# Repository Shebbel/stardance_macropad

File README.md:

# stardance_macropad
A 6 key macropad with a rotary encoder and oled display
I started with this macropad guide, because it tought it was a good start regarding future projects. 
It includes a six key macropad with a key matrix, a oled and a rotary encoder 
You can edit the function of the macropad using the VIA website.
I used AI to explain the error codes from the drc and the compiling errors.

| Component | Amount |
|-----:|-----------|
|Seeed XIAO RP2040	| 1x|
|MX-Style switches	  |6x    |
|1N4148 Diodes  |6x       |
|EC11 rotary encoder  |1x       |
|0.91 inch OLED display	  |1x       |
|keycaps  |6x       |
|SK6812 MINI-E LED  |14x       |
|M3x16mm screw	  |4x       |
|M3x5mx4mm heatset insert|4x       |
|case ( 2parts)  |1x       |
|PCB  |1x       |

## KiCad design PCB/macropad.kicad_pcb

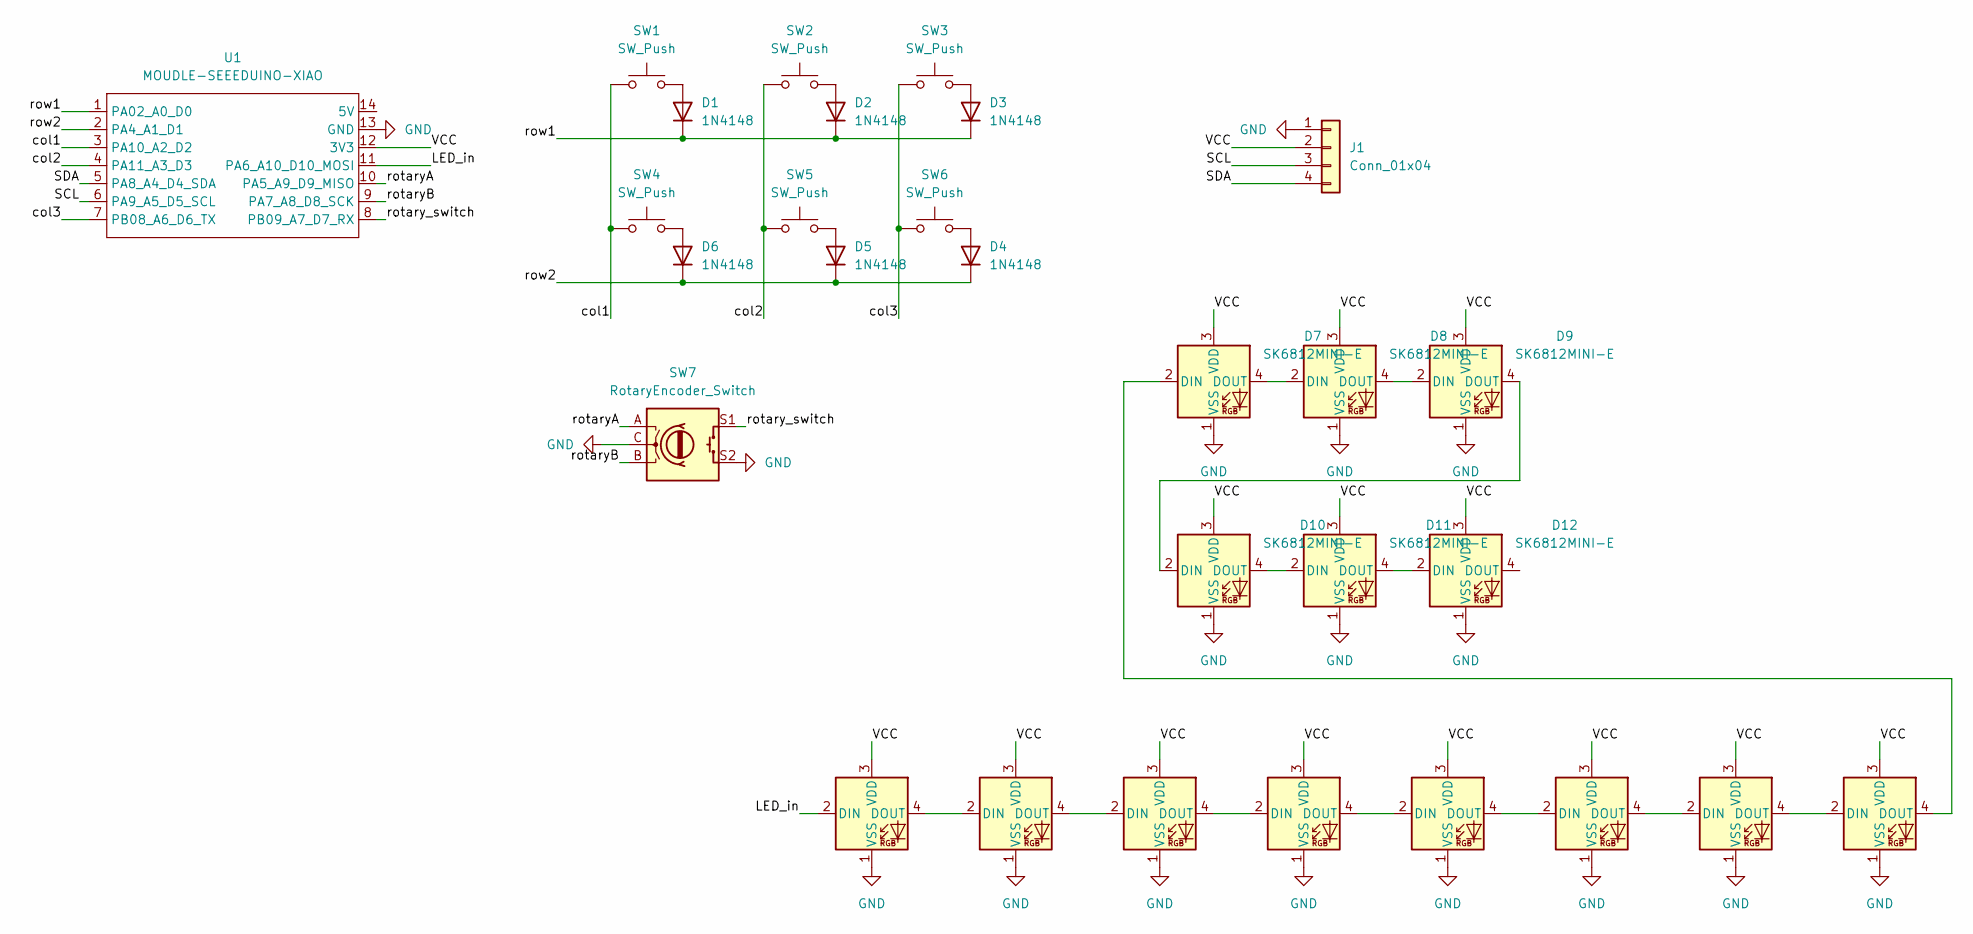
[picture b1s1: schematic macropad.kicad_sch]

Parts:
D1, D2, D3, D4, D5, D6: 1N4148; D_DO-35_SOD27_P7.62mm_Horizontal
D7, D8, D9, D10, D11, D12, D13, D14, D15, D16, D17, D18, D19, D20: SK6812MINI-E; LED_SK6812MINI-E_3.2x2.8mm_P1.5mm_ReverseMount
J1: Conn_01x04; ER_OLEDM0.91_1x-I2C
SW1, SW2, SW3, SW4, SW5, SW6: SW_Push; SW_Cherry_MX_1.00u_PCB
SW7: RotaryEncoder_Switch; RotaryEncoder_Alps_EC11E-Switch_Vertical_H20mm
U1: MOUDLE-SEEEDUINO-XIAO; XIAO-Generic-Hybrid-14P-2.54-21X17.8MM

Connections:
/LED_in: D13.2 (DIN), U1.11 (PA6_A10_D10_MOSI)
/SCL: J1.3, U1.6 (PA9_A5_D5_SCL)
/SDA: J1.4, U1.5 (PA8_A4_D4_SDA)
/VCC: D7.3 (VDD), D8.3 (VDD), D9.3 (VDD), D10.3 (VDD), D11.3 (VDD), D12.3 (VDD), D13.3 (VDD), D14.3 (VDD), D15.3 (VDD), D16.3 (VDD), D17.3 (VDD), D18.3 (VDD), D19.3 (VDD), D20.3 (VDD), J1.2, U1.12 (3V3)
/col1: SW1.1, SW4.1, U1.3 (PA10_A2_D2)
/col2: SW2.1, SW5.1, U1.4 (PA11_A3_D3)
/col3: SW3.1, SW6.1, U1.7 (PB08_A6_D6_TX)
/rotaryA: SW7.A, U1.10 (PA5_A9_D9_MISO)
/rotaryB: SW7.B, U1.9 (PA7_A8_D8_SCK)
/rotary_switch: SW7.S1, U1.8 (PB09_A7_D7_RX)
/row1: D1.1 (K), D2.1 (K), D3.1 (K), U1.1 (PA02_A0_D0)
/row2: D4.1 (K), D5.1 (K), D6.1 (K), U1.2 (PA4_A1_D1)
GND: D7.1 (VSS), D8.1 (VSS), D9.1 (VSS), D10.1 (VSS), D11.1 (VSS), D12.1 (VSS), D13.1 (VSS), D14.1 (VSS), D15.1 (VSS), D16.1 (VSS), D17.1 (VSS), D18.1 (VSS), D19.1 (VSS), D20.1 (VSS), J1.1, SW7.C, SW7.S2, U1.13 (GND)
unnamed: D1.2 (A), SW1.2
unnamed: D2.2 (A), SW2.2
unnamed: D3.2 (A), SW3.2
unnamed: D4.2 (A), SW6.2
unnamed: D5.2 (A), SW5.2
unnamed: D6.2 (A), SW4.2
unnamed: D7.4 (DOUT), D8.2 (DIN)
unnamed: D8.4 (DOUT), D9.2 (DIN)
unnamed: D9.4 (DOUT), D10.2 (DIN)
unnamed: D10.4 (DOUT), D11.2 (DIN)
unnamed: D11.4 (DOUT), D12.2 (DIN)
unnamed: D13.4 (DOUT), D14.2 (DIN)
unnamed: D14.4 (DOUT), D15.2 (DIN)
unnamed: D15.4 (DOUT), D16.2 (DIN)
unnamed: D16.4 (DOUT), D17.2 (DIN)
unnamed: D17.4 (DOUT), D18.2 (DIN)
unnamed: D18.4 (DOUT), D19.2 (DIN)
unnamed: D19.4 (DOUT), D20.2 (DIN)
unnamed: D7.2 (DIN), D20.4 (DOUT)

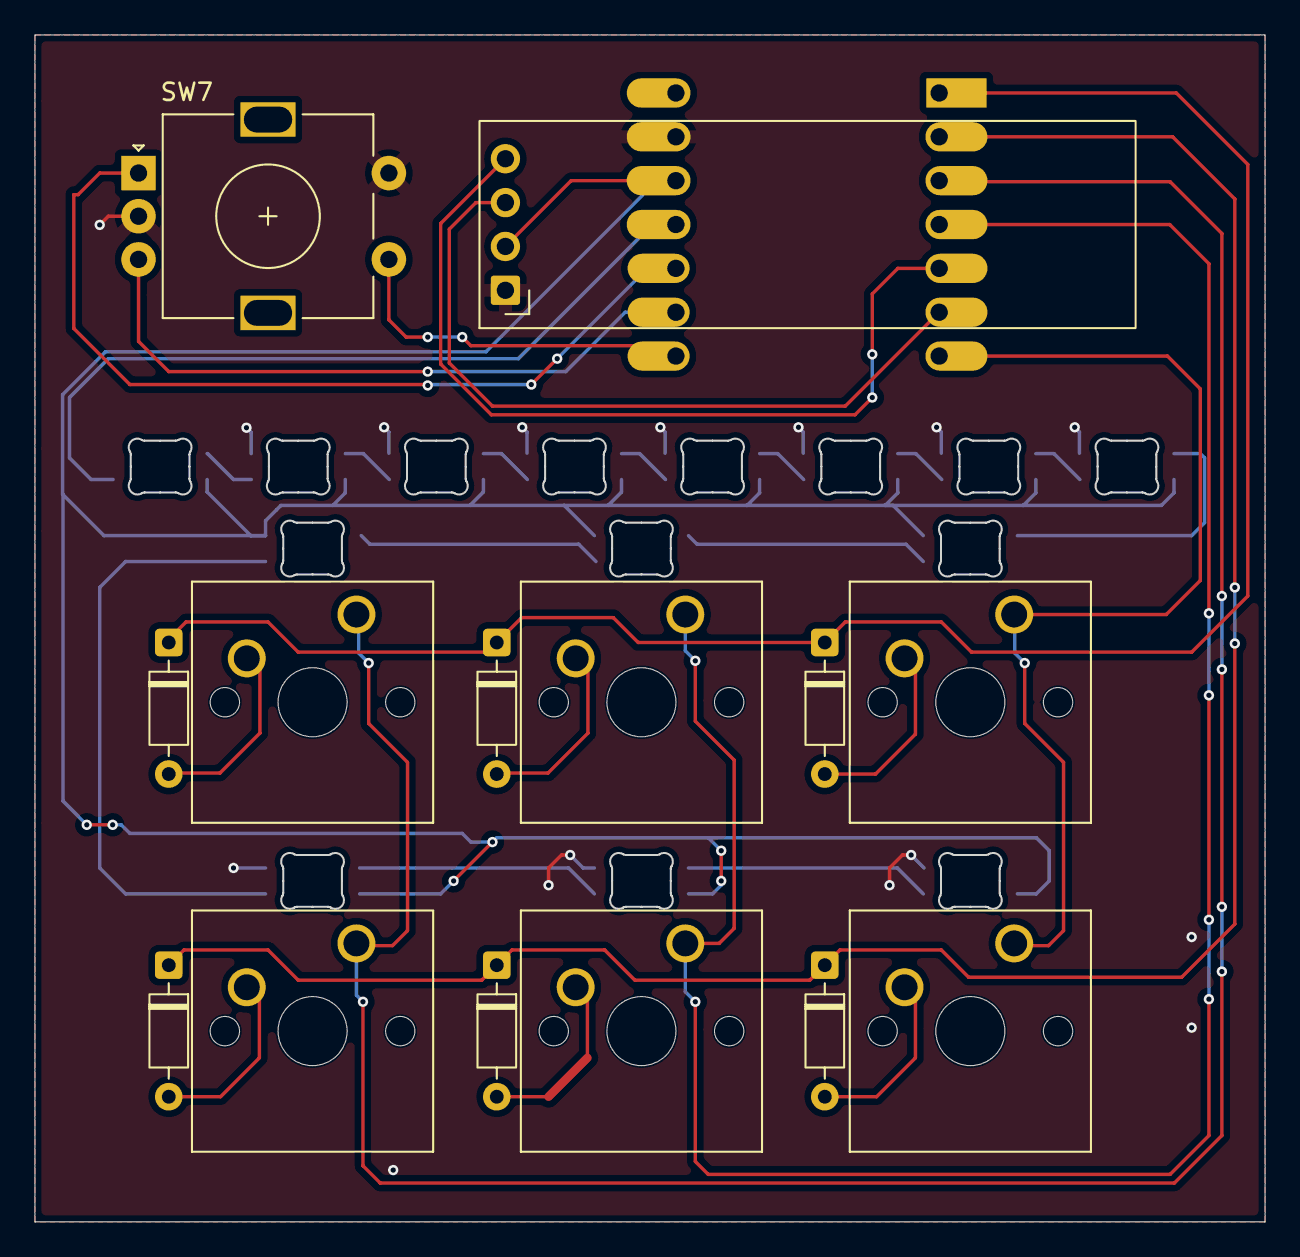
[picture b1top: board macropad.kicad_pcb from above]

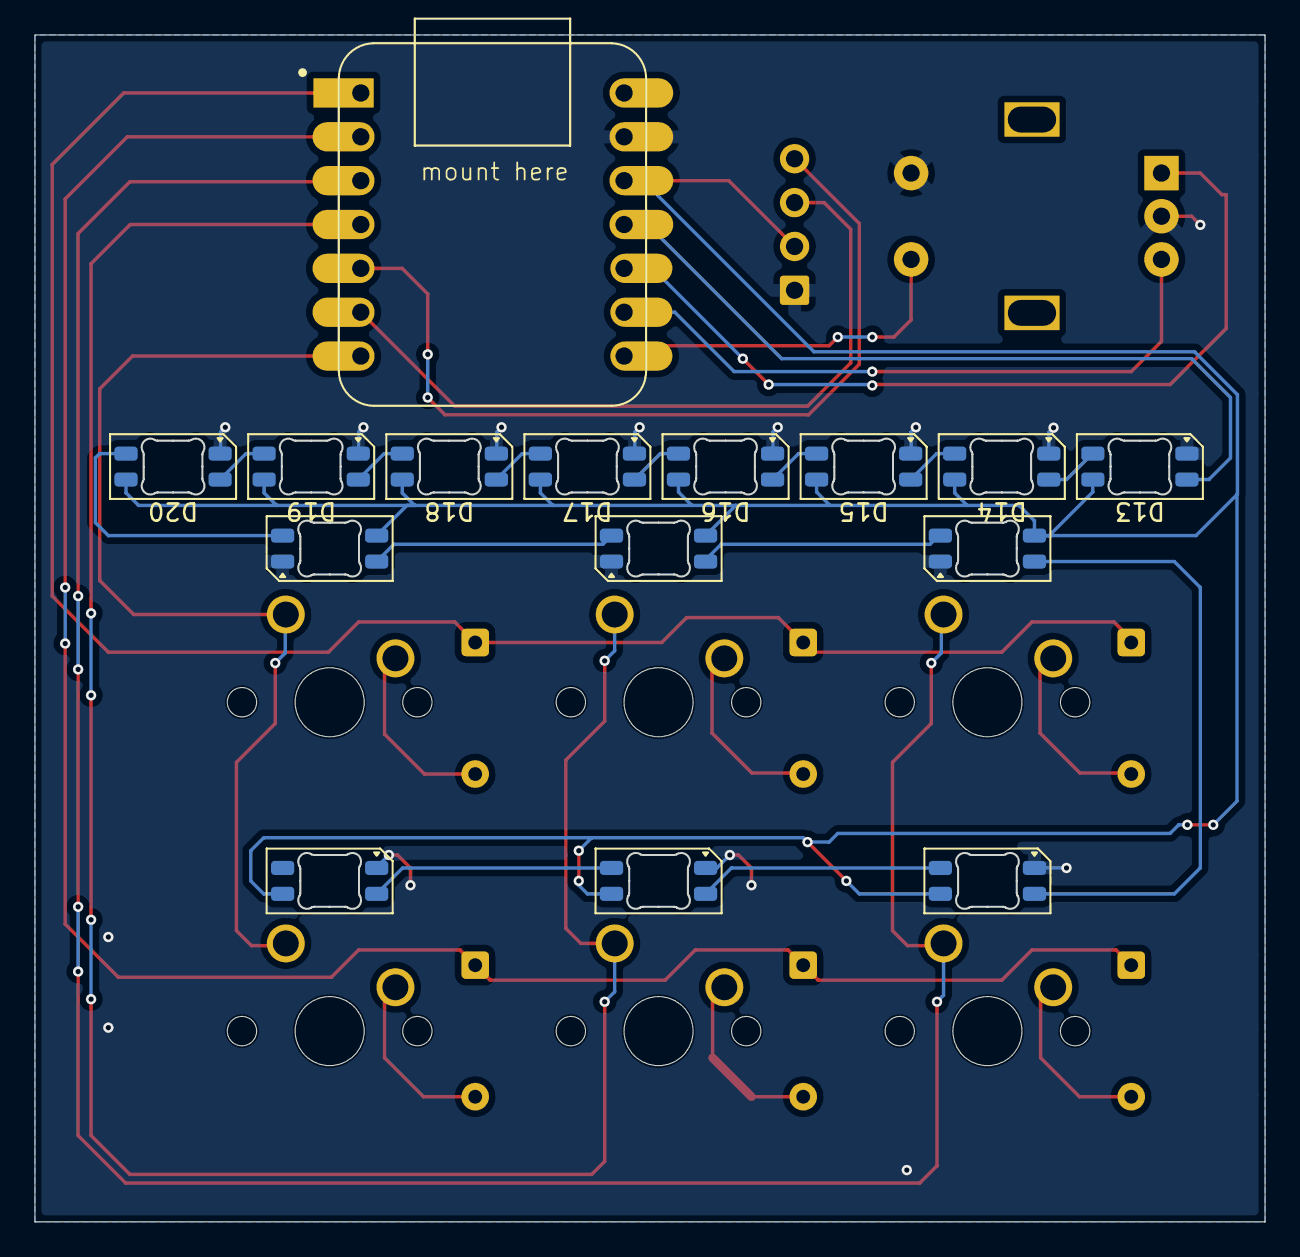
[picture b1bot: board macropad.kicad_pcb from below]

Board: 2 copper layers, 71.2 x 68.7 mm, 29 parts (15 on the bottom side), 32 nets.

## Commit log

2026-06-12 Create step
2026-06-12 Create temp
2026-06-12 Create wqprf
2026-06-12 Create qmm
2026-06-12 Create tes
2026-06-12 Create prod
